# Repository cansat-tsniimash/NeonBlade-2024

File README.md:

# NeonBlade-2024
Это репозиторий команды Neon Blade

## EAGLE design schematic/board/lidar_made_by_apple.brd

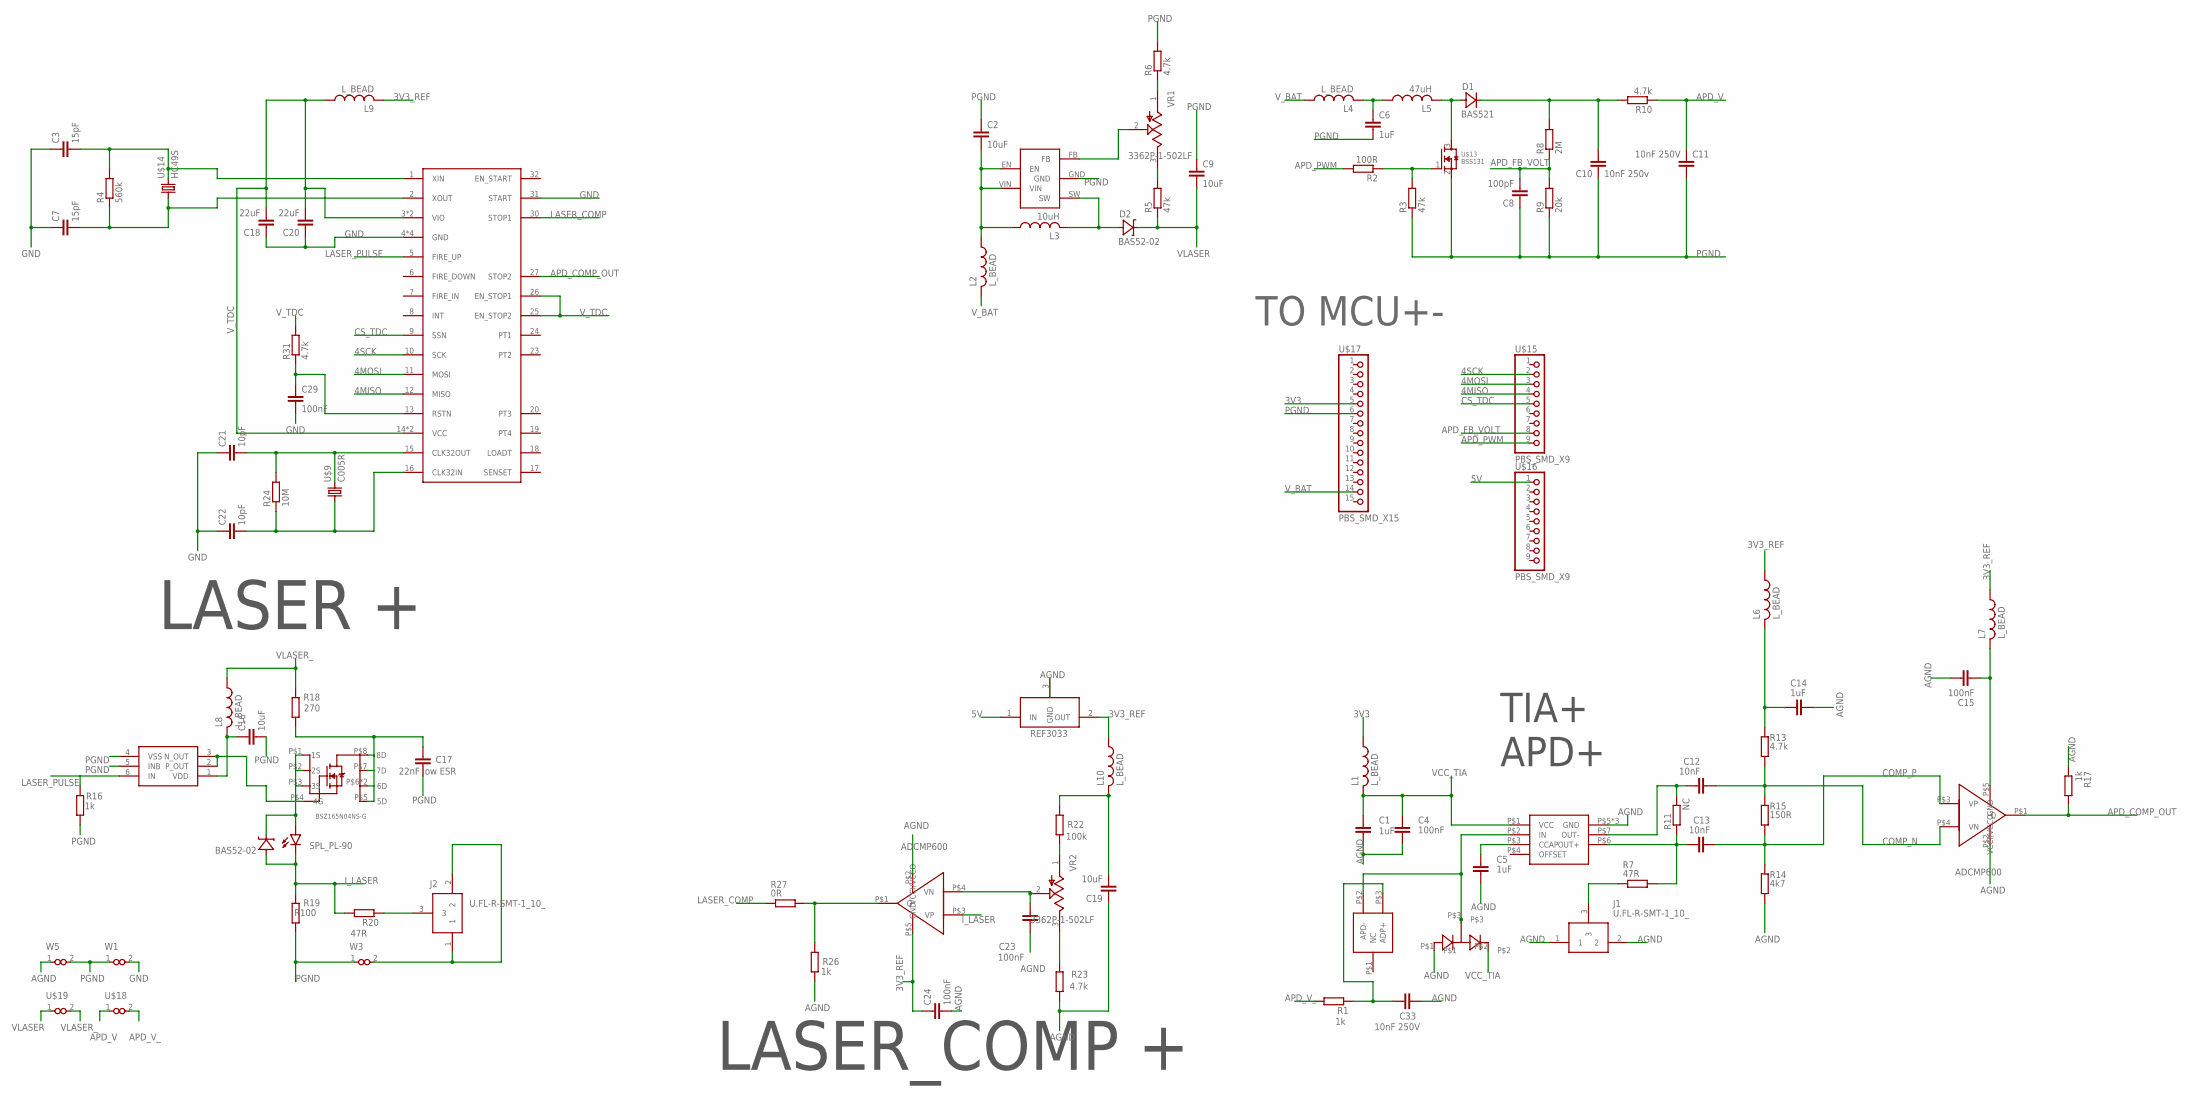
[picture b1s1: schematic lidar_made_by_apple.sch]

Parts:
C1, C5, C6, C14: 1uF; C0603
C2, C9, C16, C19: 10uF; C1206
C3, C7: 15pF; C0603
C4, C15, C23, C24, C29: 100nF; C0603
C8: 100pF; C0603
C10: 10nF 250v; C0805
C11, C33: 10nF 250V; C0805
C12, C13: 10nF; C0603
C17: 22nF low ESR; C0603
C18, C20: 22uF; C1206
C21, C22: 10pF; C0603
D1: BAS521; SOD523
D2: BAS52-02; SOD523
D6: BAV99
J1, J2: U.FL-R-SMT-1_10_; U.FL-R-SMT-1(10)
L1, L2, L4, L6, L7, L8, L9, L10: L_BEAD
L3: 10uH; L_12X12
L5: 47uH; 1210
R1, R16, R17, R26: 1k; R0603
R2: 100R; R0603
R3, R5: 47k; R0603
R4: 560k; R0603
R6, R10, R13, R23, R31: 4.7k; R0603
R7, R20: 47R; R0603
R8: 2M; R0603
R9: 20k; R0603
R11: NC; R0603
R14: 4k7; R0603
R15: 150R; R0603
R18: 270; R0603
R19: R100; R2512
R22: 100k; R0603
R24: 10M; R0603
R27: 0R; R0603
REF3033: REF3033; SOT23-3
U$2: BSZ165N04NS-G
U$3: BAS52-02; SOD523
U$4, U$8: ADCMP600
U$5: MAX40658-8-TDFN-3X3MM
U$6: SPL_PL-90
U$7: MTAPD-07-013; MAPD-07-013
U$9: C005R
U$10: TDC-GP21
U$11: MIC2288
U$12: LM5114; SOT23-6
U$13: BSS131; SOT23-3
U$14: HC49S
U$15, U$16: PBS_SMD_X9
U$17: PBS_SMD_X15; PBD_SMD_X15
U$18, U$19: VIAS-CONNECT
VR1, VR2: 3362P-1-502LF; TRIM_3362P-1-502LF
W1, W3, W5: VIAS-CONNECT

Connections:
3V3: L1.1, U$17.5
3V3_REF: C24.1, L6.1, L7.1, L9.2, L10.1, REF3033.2 (OUT), U$4.P$5 (VCCI/VCCO)
4MISO: U$10.12 (MISO), U$15.4
4MOSI: U$10.11 (MOSI), U$15.3
4SCK: U$10.10 (SCK), U$15.2
5V: REF3033.1 (IN), U$16.1
AGND: C1.2, C4.2, C5.2, C14.1, C15.1, C19.1, C23.2, C24.2, C33.2, D6.P$1, J1.1, J1.2, R14.2, R17.1, R23.1, R26.1, REF3033.3 (GND), U$4.P$2 (GND), U$5.P$5 (GND), U$5.P$8 (GND), U$5.P$9 (GND), U$8.P$2 (GND), W5.1
APD_COMP_OUT: R17.2, U$8.P$1 (Q), U$10.27 (STOP2)
APD_FB_VOLT: C8.2, R8.1, R9.2, U$15.8
APD_PWM: R2.2, U$15.9
APD_V: C11.2, R10.1, U$18.1
APD_V_: R1.2, U$18.2
COMP_N: C12.2, R13.2, R15.1, U$8.P$4 (VN)
COMP_P: C13.2, R14.1, R15.2, U$8.P$3 (VP)
CS_TDC: U$10.9 (SSN), U$15.5
GND: C3.1, C7.1, C18.1, C20.1, C21.1, C22.1, C29.2, U$10.4 (GND), U$10.21 (GND), U$10.28 (GND), U$10.31 (START), U$10.P$1 (GND), W1.2
I_LASER: R19.2, R20.2, U$3.P$2 (A), U$4.P$3 (VP), U$6.P$2 (C)
LASER_COMP: R27.1, U$10.30 (STOP1)
LASER_PULSE: R16.2, U$10.5 (FIRE_UP), U$12.6 (IN)
unnamed: U$2.P$4 (4G), U$12.2 (P_OUT), U$12.3 (N_OUT)
unnamed: C16.1, L8.2, U$12.1 (VDD)
unnamed: C17.2, R18.1, U$2.P$5 (5D), U$2.P$6 (6D), U$2.P$7 (7D), U$2.P$8 (8D), U$2.P$9 (6D)
unnamed: U$2.P$1 (1S), U$2.P$2 (2S), U$2.P$3 (3S), U$3.P$1 (C), U$6.P$1 (A)
unnamed: C23.1, U$4.P$4 (VN), VR2.2 (WIPER)
unnamed: C19.2, L10.2, R22.2
unnamed: D6.P$3, U$5.P$2 (IN), U$7.P$2 (APD-)
unnamed: C5.1, U$5.P$3 (CCAP)
unnamed: C12.1, R11.2, U$5.P$7 (OUT-)
unnamed: C13.1, R7.2, R11.1, U$5.P$6 (OUT+)
unnamed: J1.3, R7.1
unnamed: C33.1, R1.1, U$7.P$3 (ADP+)
unnamed: C14.2, L6.2, R13.1
unnamed: C15.2, L7.2, U$8.P$5 (VCCI/VCCO)
unnamed: J2.3, R20.1
unnamed: R26.2, R27.2, U$4.P$1 (Q)
unnamed: J2.1, J2.2, W3.2
unnamed: C7.2, R4.1, U$10.2 (XOUT), U$14.P$1 (1)
unnamed: C29.1, R31.1, U$10.13 (RSTN)
unnamed: C2.2, L2.1, L3.P$1 (1), U$11.EN, U$11.VIN
unnamed: C21.2, R24.2, U$9.P$2 (2), U$10.15 (CLK32OUT)
unnamed: C3.2, R4.2, U$10.1 (XIN), U$14.P$2 (2)
unnamed: C22.2, R24.1, U$9.P$1 (1), U$10.16 (CLK32IN)
unnamed: D2.P$2 (A), L3.P$2 (2), U$11.SW
unnamed: U$11.FB, VR1.2 (WIPER)
unnamed: R2.1, R3.2, U$13.1 (G)
unnamed: D1.P$2 (2), L5.2, U$13.3 (D)
unnamed: C10.2, D1.P$1 (1), R8.2, R10.2
unnamed: R6.1, VR1.1 (CCW)
unnamed: R5.2, VR1.3 (CW)
unnamed: C6.1, L4.2, L5.1
unnamed: R22.1, VR2.1 (CCW)
unnamed: R23.2, VR2.3 (CW)
PGND: C2.1, C6.2, C8.1, C9.1, C10.1, C11.1, C16.2, C17.1, R3.1, R6.2, R9.1, R16.1, R19.1, U$11.GND, U$12.4 (VSS), U$12.5 (INB), U$13.2 (S), U$17.6, W1.1, W3.1, W5.2
VCC_TIA: C1.1, C4.1, D6.P$2, L1.2, U$5.P$1 (VCC)
VLASER: C9.2, D2.P$1 (C), R5.1, U$19.1
VLASER_: L8.1, R18.2, U$19.2
V_BAT: L2.2, L4.1, U$17.14
V_TDC: C18.2, C20.2, L9.1, R31.2, U$10.3 (VIO), U$10.14 (VCC), U$10.22 (VIO), U$10.25 (EN_STOP2), U$10.26 (EN_STOP1), U$10.29 (VCC)

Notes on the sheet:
TO MCU+-
LASER +
LASER_COMP +
TIA+ APD+

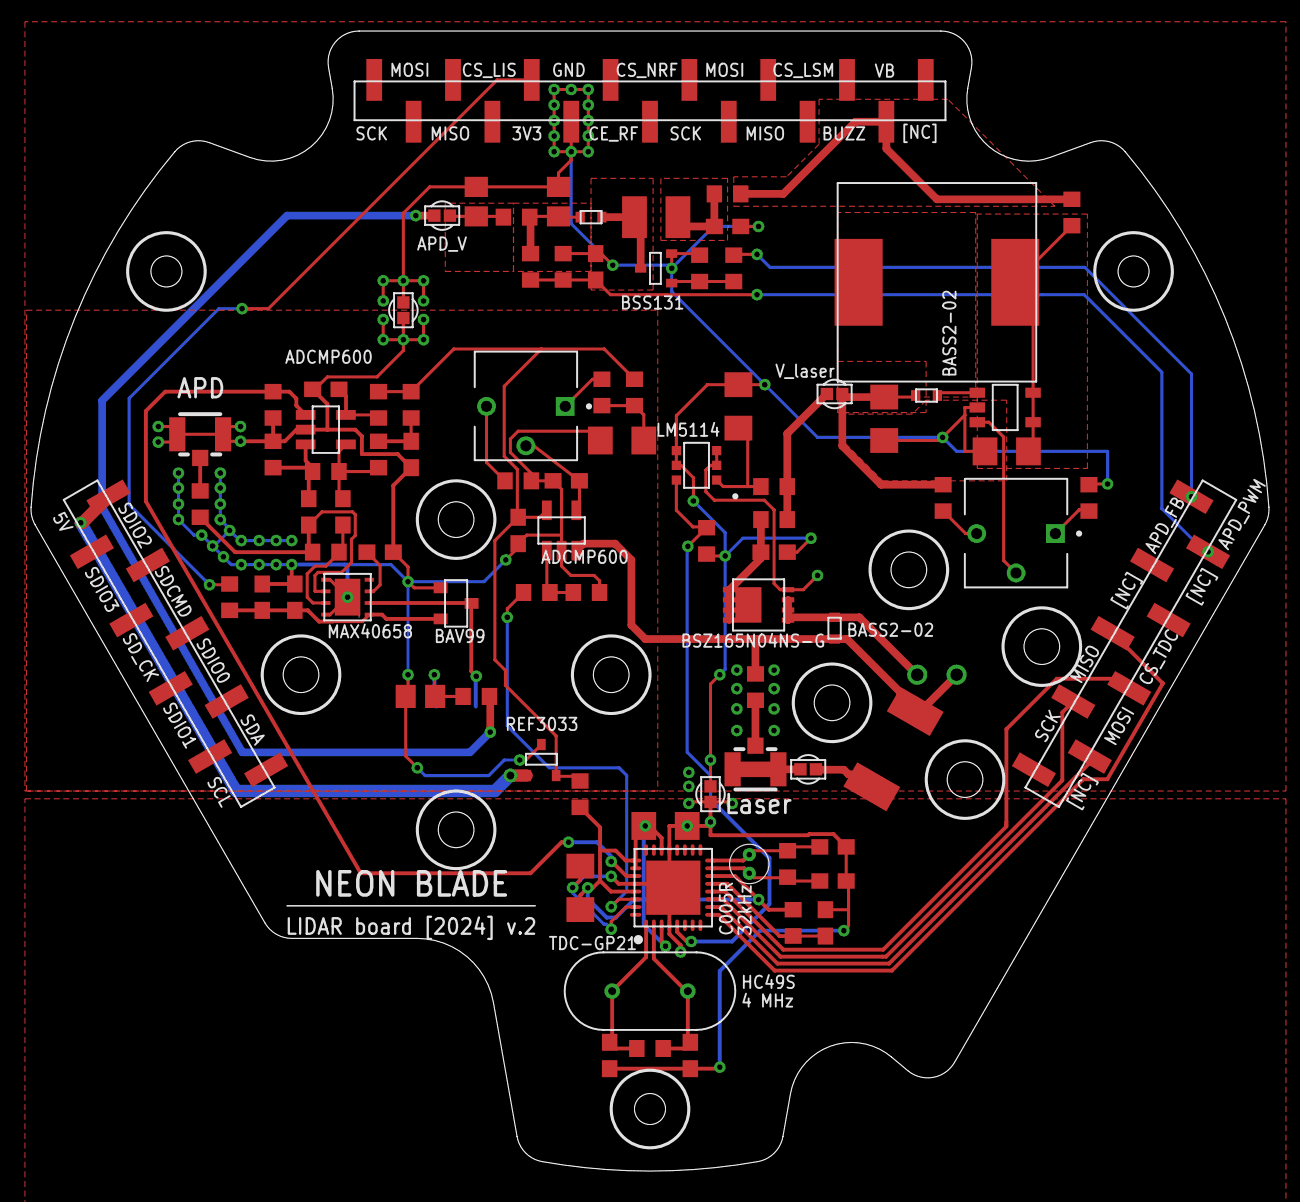
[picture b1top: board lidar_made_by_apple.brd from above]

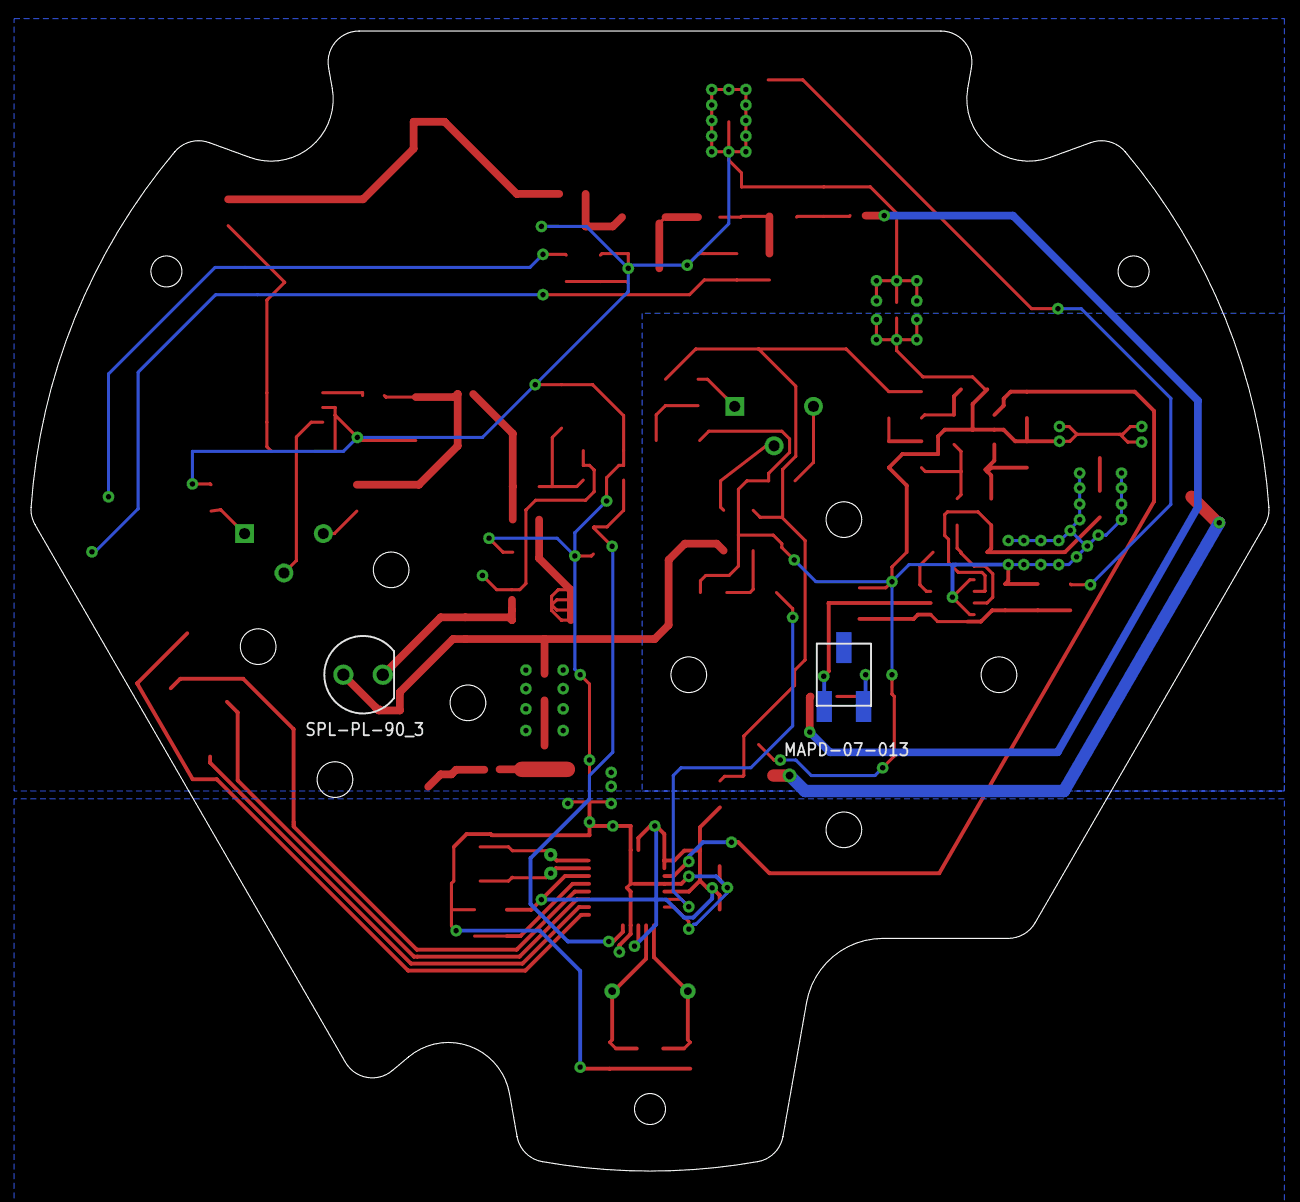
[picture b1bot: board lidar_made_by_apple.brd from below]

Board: 2 copper layers, 79.8 x 73.5 mm, 90 parts (2 on the bottom side), 58 nets.

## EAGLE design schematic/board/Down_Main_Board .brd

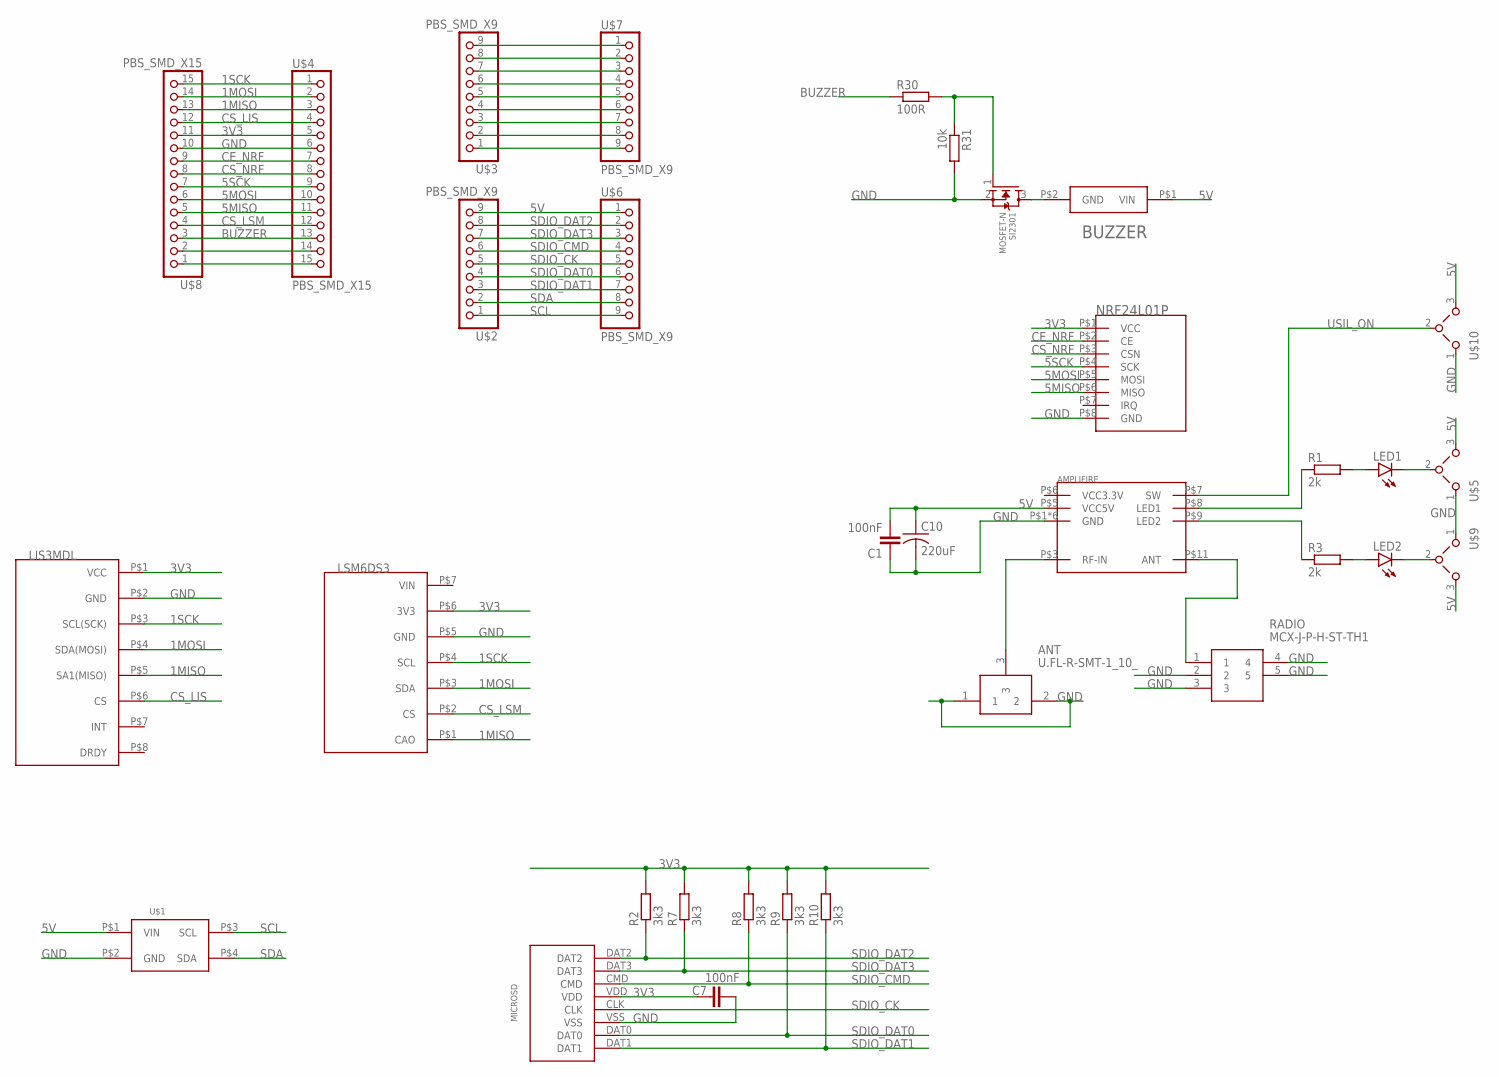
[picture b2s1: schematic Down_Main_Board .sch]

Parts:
AMPLIFIRE: XQ-02A
ANT: U.FL-R-SMT-1_10_; U.FL-R-SMT-1(10)
BUZZER: BUZZERS8R6; BUZZER-S8R12
C1, C7: 100nF; C0603
C10: 220uF; ECAP220-CMD
LED1, LED2: LEDCHIPLED_0603; CHIPLED_0603
LIS3MDL: LIS3MDL-CJMCUбез_отв.; LIS3MDL-CGMSU-NB2023-1
LSM6DS3: LSM6DS3-GY-NB2023
MICROSD: SD
NRF24L01P: NRF24L01_ML01SP4
R1, R3: 2k; R0603
R2, R7, R8, R9, R10: 3k3; R0603
R30: 100R; R0603
R31: 10k; R0603
RADIO: MCX-J-P-H-ST-TH1; MCXJPHSTTH1
SI2301: MOSFET-N; SOT23-3
U$1: BME280BME280-PINS-ONLY; BME280-PINS-ONLY
U$2, U$3, U$6, U$7: PBS_SMD_X9
U$4, U$8: PBS_SMD_X15; PBD_SMD_X15
U$5, U$9, U$10: VIAS-SELECT

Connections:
1MISO: LIS3MDL.P$5 (SA1(MISO)), LSM6DS3.P$1 (CAO), U$4.3, U$8.13
1MOSI: LIS3MDL.P$4 (SDA(MOSI)), LSM6DS3.P$3 (SDA), U$4.2, U$8.14
1SCK: LIS3MDL.P$3 (SCL(SCK)), LSM6DS3.P$4 (SCL), U$4.1, U$8.15
3V3: C7.2, LIS3MDL.P$1 (VCC), LSM6DS3.P$6 (3V3), MICROSD.VDD, NRF24L01P.P$1 (VCC), R2.2, R7.2, R8.2, R9.2, R10.2, U$4.5, U$8.11
5MISO: NRF24L01P.P$6 (MISO), U$4.11, U$8.5
5MOSI: NRF24L01P.P$5 (MOSI), U$4.10, U$8.6
5SCK: NRF24L01P.P$4 (SCK), U$4.9, U$8.7
5V: AMPLIFIRE.P$5 (VCC5V), BUZZER.P$1 (VIN), C1.2, C10.P$1 (1), U$1.P$1 (VIN), U$2.9, U$5.3 (RIGHT), U$6.1, U$9.3 (RIGHT), U$10.3 (RIGHT)
BUZZER: R30.1, U$4.13, U$8.3
CE_NRF: NRF24L01P.P$2 (CE), U$4.7, U$8.9
CS_LIS: LIS3MDL.P$6 (CS), U$4.4, U$8.12
CS_LSM: LSM6DS3.P$2 (CS), U$4.12, U$8.4
CS_NRF: NRF24L01P.P$3 (CSN), U$4.8, U$8.8
GND: AMPLIFIRE.P$1 (GND), AMPLIFIRE.P$2 (GND), AMPLIFIRE.P$4 (GND), AMPLIFIRE.P$10 (GND), AMPLIFIRE.P$12 (GND), AMPLIFIRE.P$13 (GND), ANT.1, ANT.2, C1.1, C7.1, C10.P$2 (2), LIS3MDL.P$2 (GND), LSM6DS3.P$5 (GND), MICROSD.VSS, NRF24L01P.P$8 (GND), R31.2, RADIO.2, RADIO.3, RADIO.4, RADIO.5, SI2301.2 (S), U$1.P$2 (GND), U$4.6, U$5.1 (LEFT), U$8.10, U$9.1 (LEFT), U$10.1 (LEFT)
unnamed: R30.2, R31.1, SI2301.1 (G)
unnamed: U$4.14, U$8.2
unnamed: U$4.15, U$8.1
unnamed: AMPLIFIRE.P$3 (RF-IN), ANT.3
unnamed: AMPLIFIRE.P$11 (ANT), RADIO.1
unnamed: U$3.8, U$7.2
unnamed: U$3.7, U$7.3
unnamed: U$3.6, U$7.4
unnamed: U$3.5, U$7.5
unnamed: U$3.4, U$7.6
unnamed: U$3.3, U$7.7
unnamed: U$3.9, U$7.1
unnamed: U$3.2, U$7.8
unnamed: U$3.1, U$7.9
unnamed: LED1.C, U$5.2 (TOP)
unnamed: LED1.A, R1.2
unnamed: AMPLIFIRE.P$8 (LED1), R1.1
unnamed: LED2.C, U$9.2 (TOP)
unnamed: BUZZER.P$2 (GND), SI2301.3 (D)
unnamed: LED2.A, R3.2
unnamed: AMPLIFIRE.P$9 (LED2), R3.1
SCL: U$1.P$3 (SCL), U$2.1, U$6.9
SDA: U$1.P$4 (SDA), U$2.2, U$6.8
SDIO_CK: MICROSD.CLK, U$2.5, U$6.5
SDIO_CMD: MICROSD.CMD, R8.1, U$2.6, U$6.4
SDIO_DAT0: MICROSD.DAT0, R9.1, U$2.4, U$6.6
SDIO_DAT1: MICROSD.DAT1, R10.1, U$2.3, U$6.7
SDIO_DAT2: MICROSD.DAT2, R2.1, U$2.8, U$6.2
SDIO_DAT3: MICROSD.DAT3, R7.1, U$2.7, U$6.3
USIL_ON: AMPLIFIRE.P$7 (SW), U$10.2 (TOP)

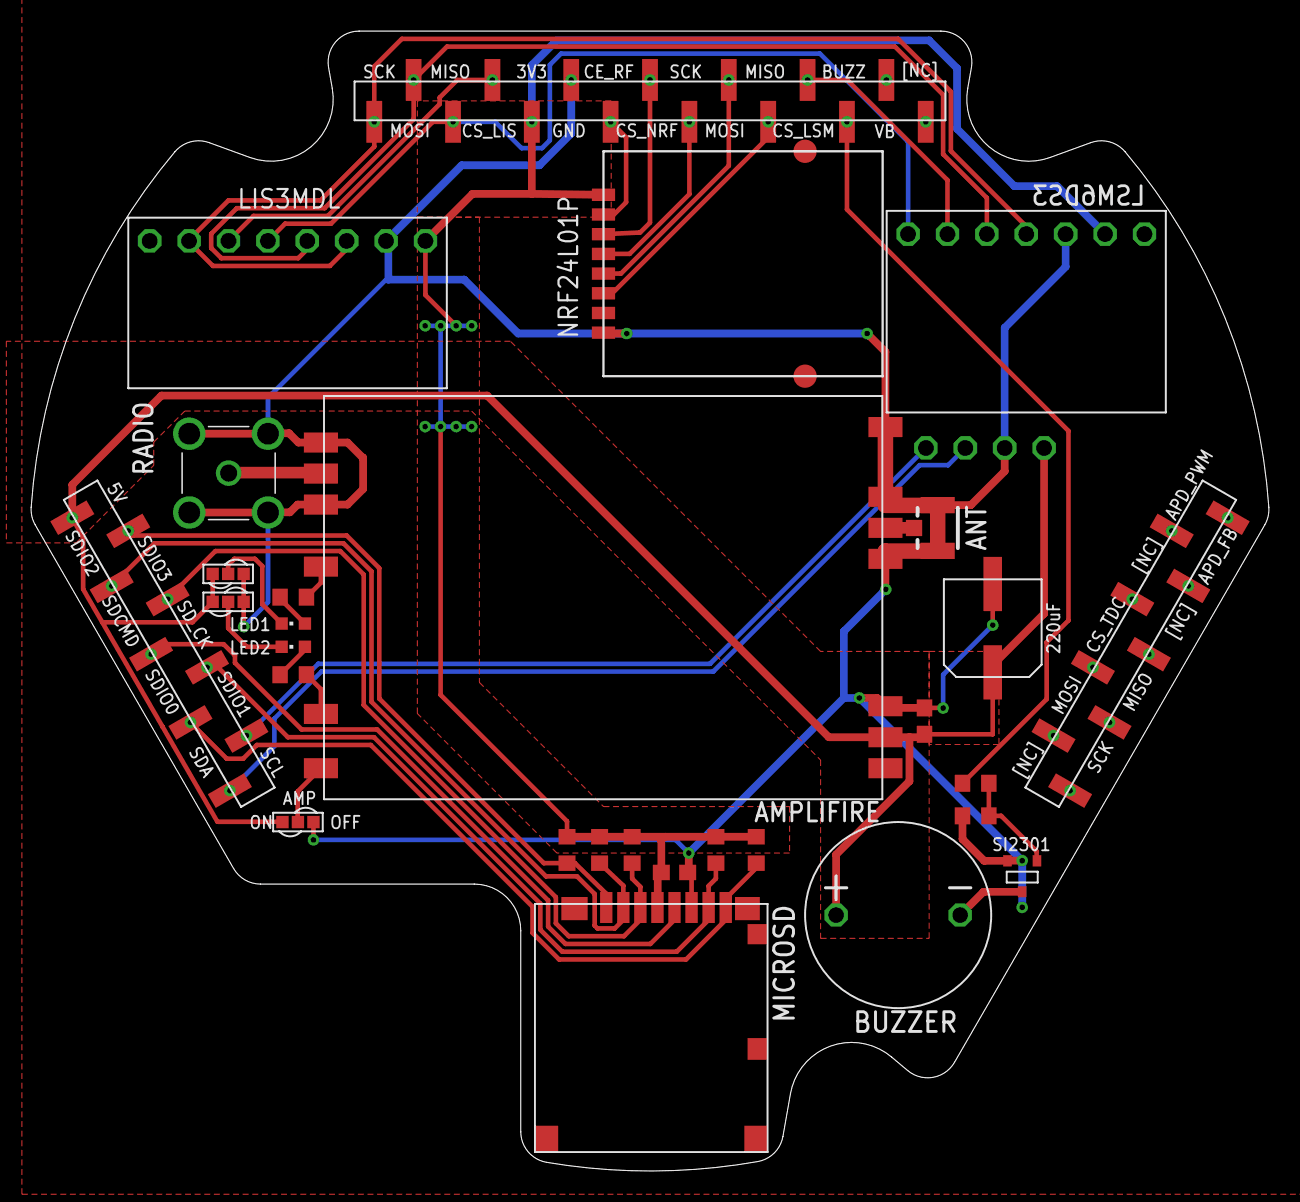
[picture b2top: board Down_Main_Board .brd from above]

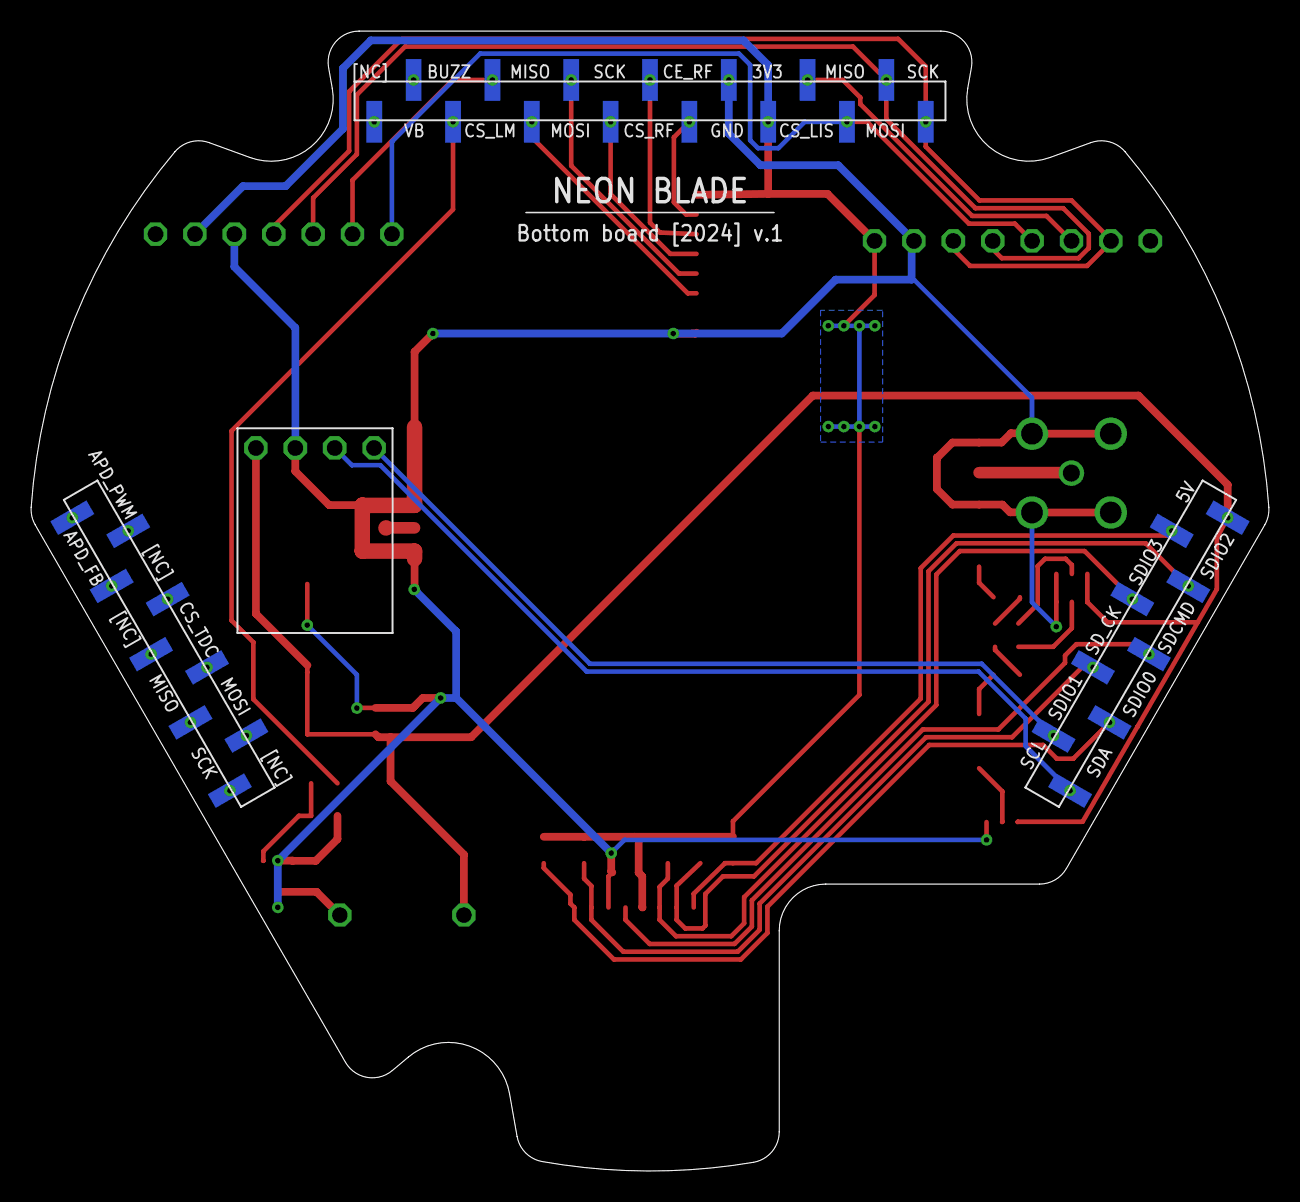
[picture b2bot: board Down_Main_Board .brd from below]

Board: 2 copper layers, 79.8 x 73.5 mm, 33 parts (5 on the bottom side), 44 nets.

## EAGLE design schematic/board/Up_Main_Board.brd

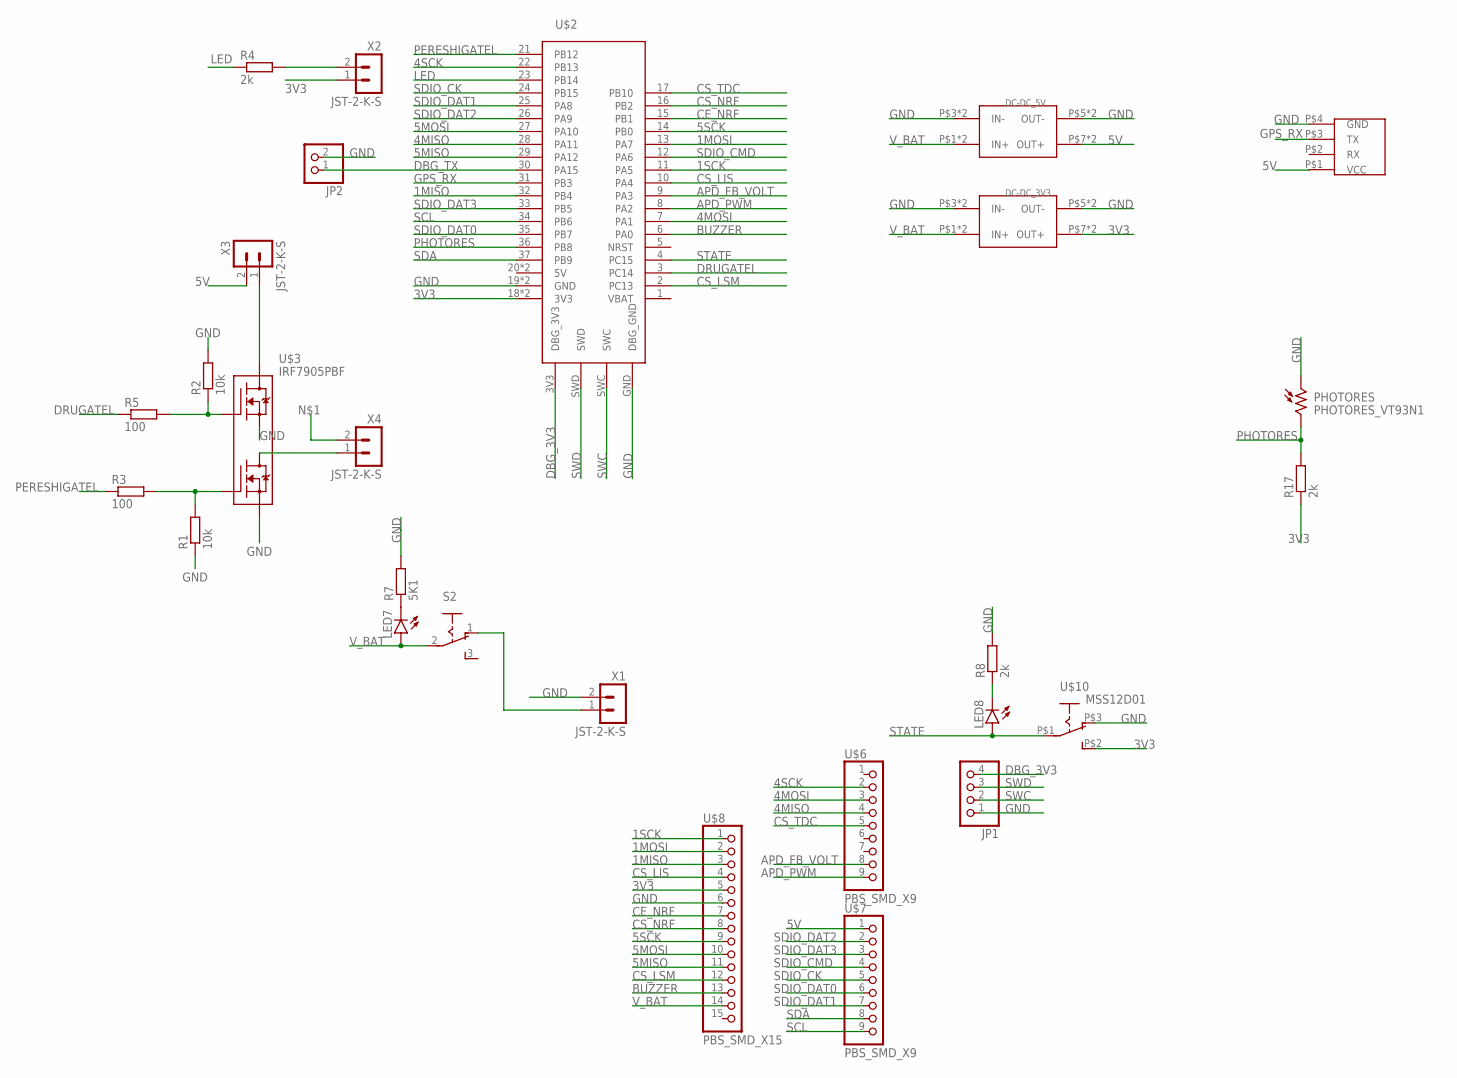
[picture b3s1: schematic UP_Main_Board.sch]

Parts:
DC-DC_3V3, DC-DC_5V: MP1584-B
JP1: PINHD-1X4/90; 1X04/90
JP2: PINHD-1X2; 1X02
LED7, LED8: LEDSML0603; SML0603
PHOTORES: PHOTORES_VT93N1; PHOTORES_VT93N1_SMD
R1, R2: 10k; R0603
R3, R5: 100; R0603
R4, R8, R17: 2k; R0603
R7: 5K1; R0603
S2: UNICS-SWITCH
U$1: GPS_NEO6M; GPS_NEO6M_NEW
U$2: STM32F401_BOARD
U$3: IRF7905PBF; SO8
U$6, U$7: PBS_SMD_X9
U$8: PBS_SMD_X15; PBD_SMD_X15
U$10: MSS12D01
X1, X2, X3, X4: JST-2-K-S; B2B-PH-K-S

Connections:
1MISO: U$2.32 (PB4), U$8.3
1MOSI: U$2.13 (PA7), U$8.2
1SCK: U$2.11 (PA5), U$8.1
3V3: DC-DC_3V3.P$7 (OUT+), DC-DC_3V3.P$8 (OUT+), R17.1, U$2.18 (3V3), U$2.40 (3V3), U$8.5, U$10.P$2 (S), X2.1
4MISO: U$2.28 (PA11), U$6.4
4MOSI: U$2.7 (PA1), U$6.3
4SCK: U$2.22 (PB13), U$6.2
5MISO: U$2.29 (PA12), U$8.11
5MOSI: U$2.27 (PA10), U$8.10
5SCK: U$2.14 (PB0), U$8.9
5V: DC-DC_5V.P$7 (OUT+), DC-DC_5V.P$8 (OUT+), U$1.P$1 (VCC), U$7.1, X3.2
APD_FB_VOLT: U$2.9 (PA3), U$6.8
APD_PWM: U$2.8 (PA2), U$6.9
BUZZER: U$2.6 (PA0), U$8.13
CE_NRF: U$2.15 (PB1), U$8.7
CS_LIS: U$2.10 (PA4), U$8.4
CS_LSM: U$2.2 (PC13), U$8.12
CS_NRF: U$2.16 (PB2), U$8.8
CS_TDC: U$2.17 (PB10), U$6.5
DBG_3V3: JP1.4, U$2.3V3 (DBG_3V3)
DBG_TX: JP2.1, U$2.30 (PA15)
DRUGATEL: R5.1, U$2.3 (PC14)
GND: DC-DC_3V3.P$3 (IN-), DC-DC_3V3.P$4 (IN-), DC-DC_3V3.P$5 (OUT-), DC-DC_3V3.P$6 (OUT-), DC-DC_5V.P$3 (IN-), DC-DC_5V.P$4 (IN-), DC-DC_5V.P$5 (OUT-), DC-DC_5V.P$6 (OUT-), JP1.1, JP2.2, PHOTORES.P$1 (1), R1.1, R2.2, R7.2, R8.2, U$1.P$4 (GND), U$2.19 (GND), U$2.39 (GND), U$2.GND (DBG_GND), U$3.1 (S2), U$3.3 (S1), U$8.6, U$10.P$3 (O), X1.2
GPS_RX: U$1.P$3 (TX), U$2.31 (PB3)
LED: R4.1, U$2.23 (PB14)
unnamed: S2.1 (O), X1.1, X4.2
unnamed: U$3.5 (D1), U$3.6 (D1), X3.1
unnamed: R2.1, R5.2, U$3.4 (G1)
unnamed: LED7.C, R7.1
unnamed: R1.2, R3.2, U$3.2 (G2)
unnamed: R4.2, X2.2
unnamed: U$3.7 (D2), U$3.8 (D2), X4.1
unnamed: LED8.C, R8.1
PERESHIGATEL: R3.1, U$2.21 (PB12)
PHOTORES: PHOTORES.P$2 (2), R17.2, U$2.36 (PB8)
SCL: U$2.34 (PB6), U$7.9
SDA: U$2.37 (PB9), U$7.8
SDIO_CK: U$2.24 (PB15), U$7.5
SDIO_CMD: U$2.12 (PA6), U$7.4
SDIO_DAT0: U$2.35 (PB7), U$7.6
SDIO_DAT1: U$2.25 (PA8), U$7.7
SDIO_DAT2: U$2.26 (PA9), U$7.2
SDIO_DAT3: U$2.33 (PB5), U$7.3
STATE: LED8.A, U$2.4 (PC15), U$10.P$1
SWC: JP1.2, U$2.SWC
SWD: JP1.3, U$2.SWD
V_BAT: DC-DC_3V3.P$1 (IN+), DC-DC_3V3.P$2 (IN+), DC-DC_5V.P$1 (IN+), DC-DC_5V.P$2 (IN+), LED7.A, S2.2, U$8.14

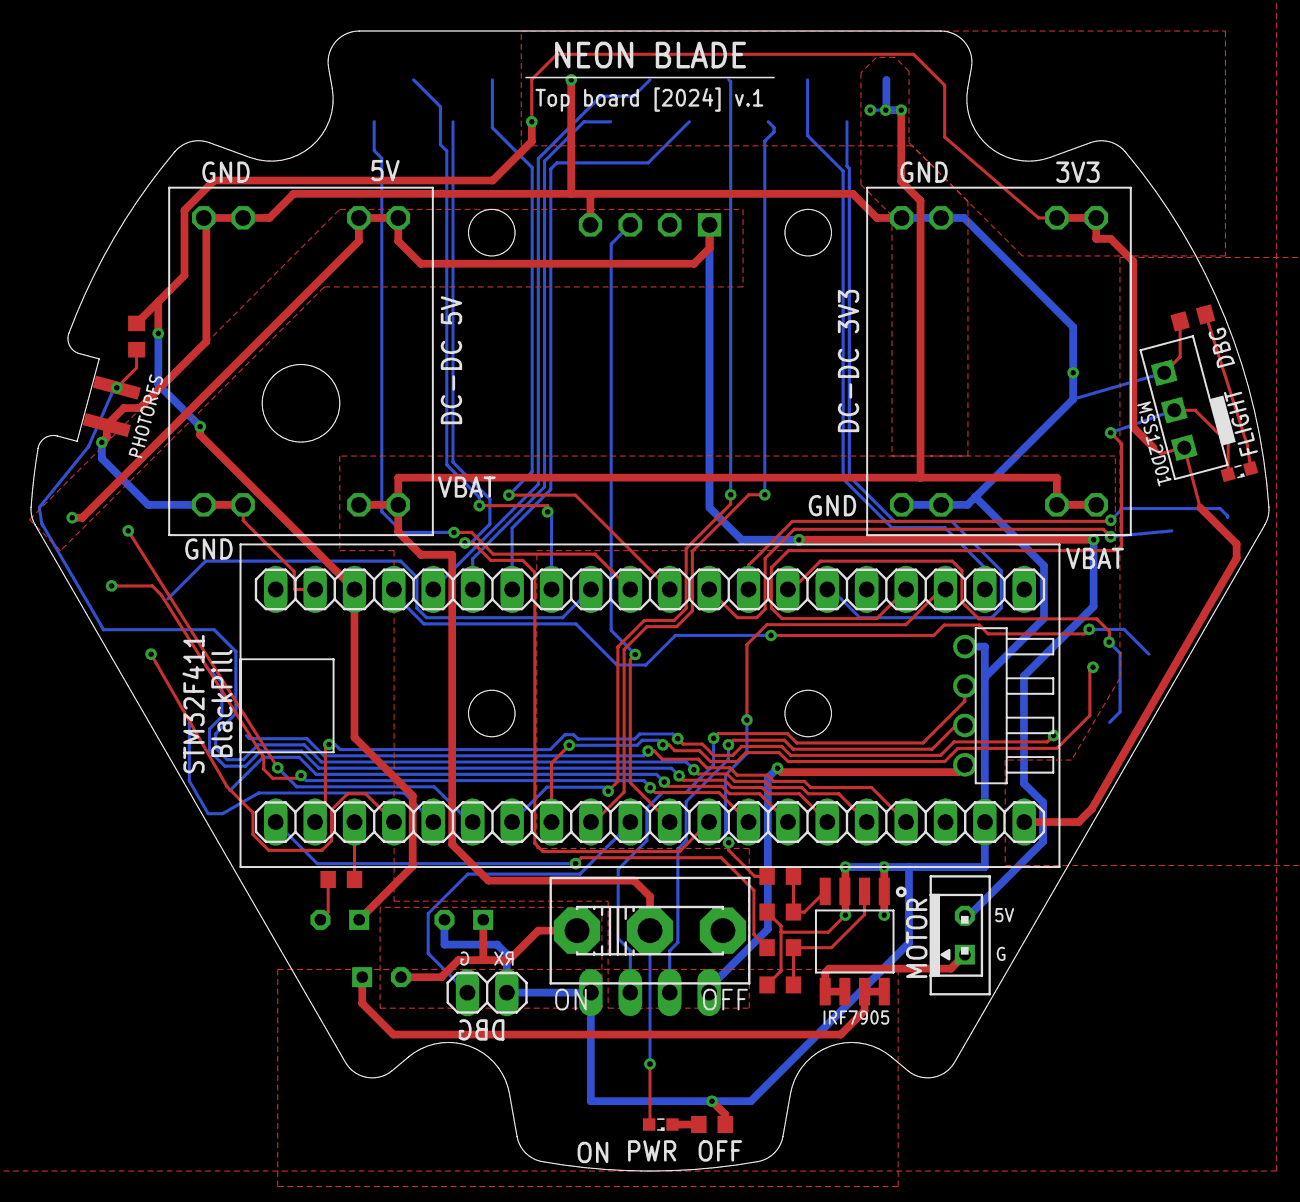
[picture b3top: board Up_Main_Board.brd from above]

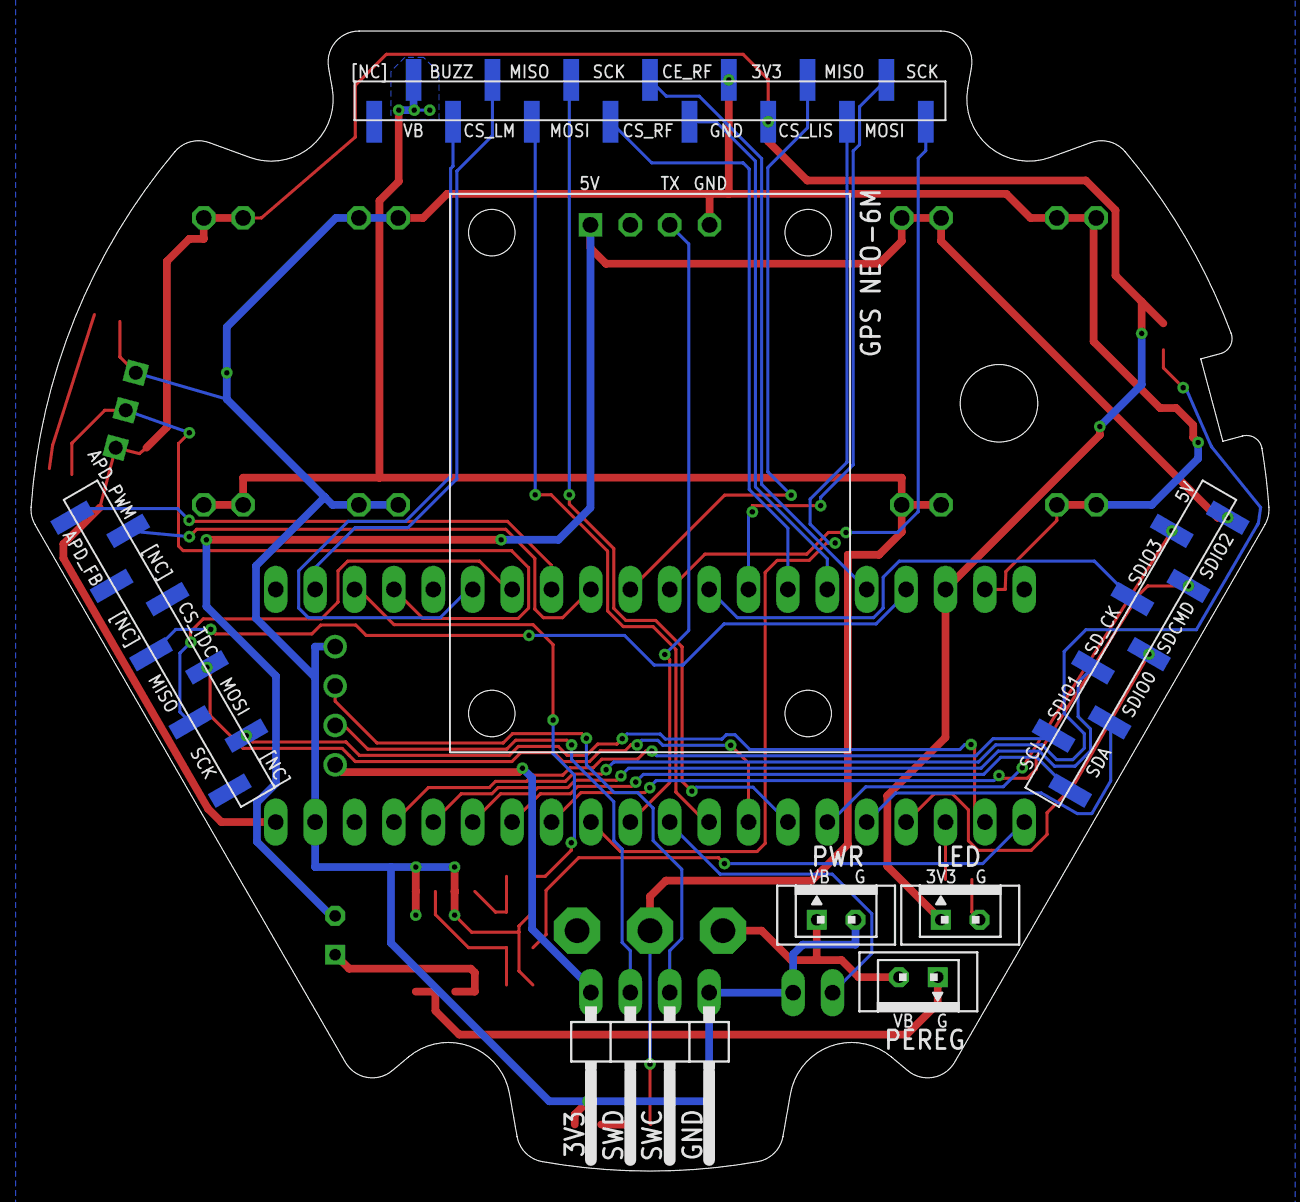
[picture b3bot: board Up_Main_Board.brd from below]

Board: 2 copper layers, 79.8 x 73.5 mm, 27 parts (8 on the bottom side), 47 nets.
